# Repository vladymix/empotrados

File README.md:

# Sistemas empotrador
SE

# Prototipo practica 

# Prubeas

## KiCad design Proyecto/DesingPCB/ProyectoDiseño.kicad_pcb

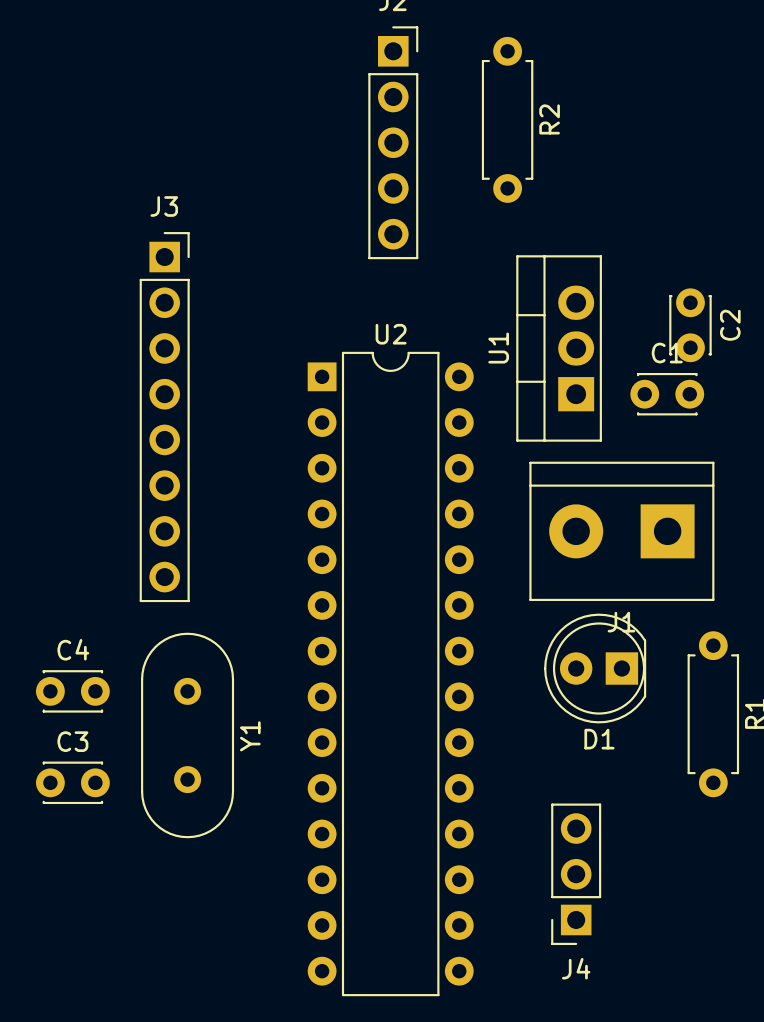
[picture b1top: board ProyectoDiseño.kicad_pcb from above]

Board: 2 copper layers, 14 parts (0 on the bottom side), 20 nets, no tracks yet.

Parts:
C1: 0.33 uF; C_Disc_D3.0mm_W2.0mm_P2.50mm
C2: 0.1 uF; C_Disc_D3.0mm_W2.0mm_P2.50mm
C3, C4: C; C_Disc_D3.0mm_W2.0mm_P2.50mm
D1: LED; LED_D5.0mm
J1: Conn_01x02; TerminalBlock_bornier-2_P5.08mm
J2: Conn_01x05; PinSocket_1x05_P2.54mm_Vertical
J3: Conn_01x08; PinSocket_1x08_P2.54mm_Vertical
J4: Conn_01x03; PinSocket_1x03_P2.54mm_Vertical
R1: 1K; R_Axial_DIN0207_L6.3mm_D2.5mm_P7.62mm_Horizontal
R2: 5K; R_Axial_DIN0207_L6.3mm_D2.5mm_P7.62mm_Horizontal
U1: LM7805_TO220; TO-220-3_Vertical
U2: PIC16F886-IP; DIP-28_W7.62mm
Y1: Crystal; Crystal_HC18-U_Vertical

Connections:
+5V: C2.1, D1.2, J2.2, R2.2, U1.3, U2.20
Calefactor: J3.3, U2.12
GND: C3.1, C4.1, J2.3, J4.3, R1.2, U2.8, U2.19
Humedad: J3.6, U2.4
Luminosidad: J3.7, U2.5
unnamed: C1.1, J1.2, U1.1
unnamed: C1.2, C2.2, J1.1, U1.2
unnamed: C3.2, U2.10, Y1.2
unnamed: C4.2, U2.9, Y1.1
unnamed: D1.1, R1.1
unnamed: J2.1, R2.1, U2.1
unnamed: J2.4, U2.28
unnamed: J2.5, U2.27
unnamed: J4.1, U2.18
unnamed: J4.2, U2.17
Potenciometro: J3.8, U2.7
Refrigerador: J3.1, U2.11
TemperaturaExterior: J3.5, U2.3
TemperaturaInterior: J3.4, U2.2
VentiladorPWM: J3.2, U2.13

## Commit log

2021-09-28 add files pr2
2021-09-28 Update template
2021-09-28 tiempo 1 seg
2021-09-28 practica 5ms
2021-09-28 Update 1 sg
2021-09-28 punto y coma
2021-09-28 Update P2
2021-09-28 add printf
2021-10-24 update git ignore
2021-10-24 Carpeta para el SysML
2021-10-24 actualizacion sysml
2021-10-24 SysML + metadata
2021-10-24 Export de sysML
2021-10-24 Update anotation
2021-10-24 Diagram
2021-11-01 Practica 2
2021-11-01 prt 3
2021-11-01 ejercicio2 resuelto
2021-11-01 Correccion practica 3
2021-11-01 Plantilla eje 4
2021-11-01 fix ejer4
2021-11-03 Limpieza del proyecto y esquematico subido
2021-11-03 Añadida imagen del prototipo
2021-11-17 Versión 2 de diseño de alto nivel que incluye bloques funcionale sde descripción Software para permitir descripción interna de bloque con state machine
2021-11-17 Pruebas git
2021-11-17 Version 1 Practica 4
2021-11-18 check credentials
2021-11-18 aproximacion
2021-11-18 Pruebas commit mac
2021-11-21 Archivos arquitectura High Lev V2
2021-11-21 Actualizada Arq Descriptiva
2021-11-21 Actualizacion 2 Arq Descriptiva
2021-11-21 Versión final descriptiva diagrama de estados
2021-11-21 Manu
2021-11-28 Añandidos diagramas de diseño detallado
2021-11-28 Añadidos diagramas de cada bloque funcional software y añadido Informe
2021-11-28 Añanadida imagen de diseño esquematico
2021-12-26 proyecto final código
